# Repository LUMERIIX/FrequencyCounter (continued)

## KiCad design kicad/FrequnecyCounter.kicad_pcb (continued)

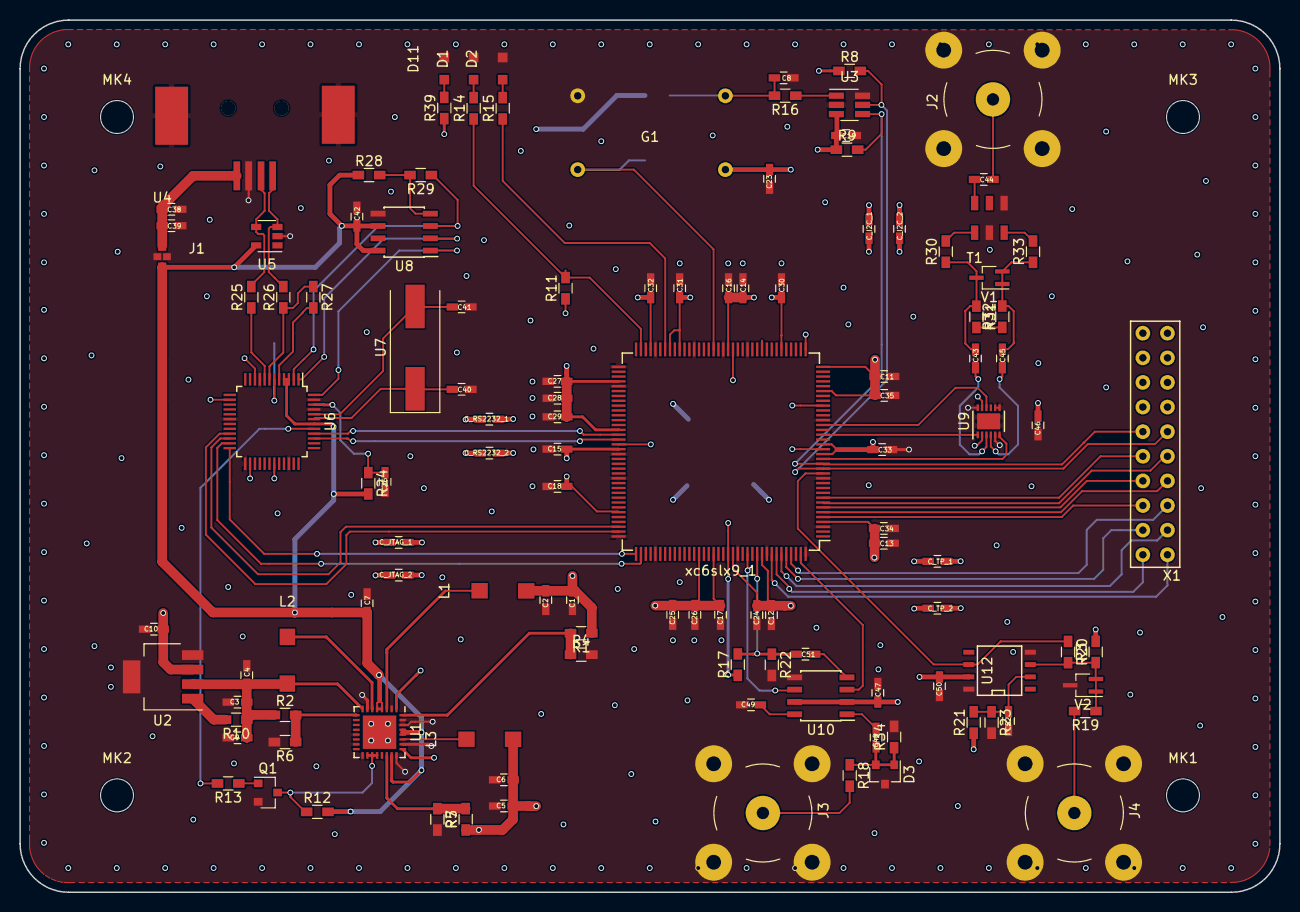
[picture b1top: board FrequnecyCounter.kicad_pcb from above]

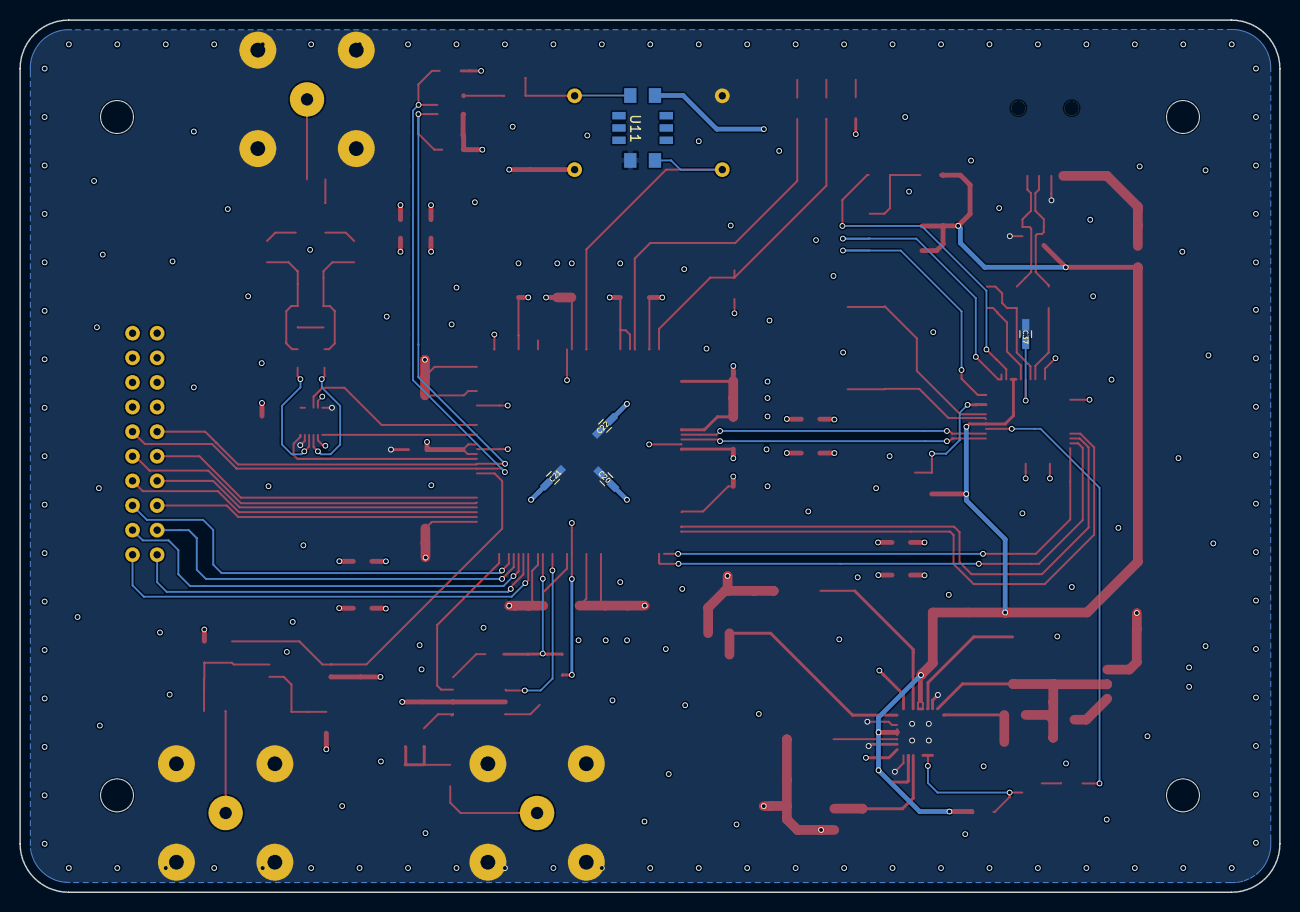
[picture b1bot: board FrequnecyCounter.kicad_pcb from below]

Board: 4 copper layers, 130.0 x 90.0 mm, 129 parts (5 on the bottom side), 80 nets.

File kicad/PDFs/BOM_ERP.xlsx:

| Description | Part | References | Value | Quantity Per PCB | ERP Nr. | Kontrolle Footprint | Quantity to Order
1 | Unpolarized capacitor | C | C18 C22 C25 C26 C28 C29 C31 C32 C34 C35 | 0.47u | 10 | 120048 | x | 0 | MG-07
2 | Unpolarized capacitor | C | C7 C19 C23 C39 C42 C43 C44 C45 C46 C47 | 100n | 10 | 101653 | x | 0 | MG-07
3 | Unpolarized capacitor | C | C51 | 100p | 1 | 118123 | x | 0 | MG-07
4 | Unpolarized capacitor | C | C1 C2 C3 C4 C5 C6 C9 C10 C38 | 10u | 9 | 101654 | x | 0 | MG-07
5 | Unpolarized capacitor | C | C48 C49 | 1n | 2 | 101606 | x | 0 | MG-07
6 | Unpolarized capacitor | C | C8 C_I2C_1 C_I2C_2 C_JTAG_1 C_JTAG_2 C_RS2232_1 C_RS2232_2 C_TP_1 C_TP_2 | 1u | 9 | 101655 | x | 0 | MG-07
7 | Unpolarized capacitor | C | C40 C41 | 27p | 2 | 115705 | x | 0 | MG-07
8 | Unpolarized capacitor | C | C36 C37 | 33n | 2 | 120245 | x | 0 | MG-07
9 | Unpolarized capacitor | C | C11 C12 C13 C14 C15 C16 C17 C20 C21 C24 C27 C30 C33 | 4.7u | 13 | 121207 | x | 0 | MG-07
10 | BAV99 High-speed switching diodes | BAV99 | D3 | BAV99 | 1 | 100569 | x | 0 | SMD_DIO 04
11 | LED generic | LED | D1 D2 D11 | LED | 3 | 121890 | x | 0 | MG-13
12 | AOCJY1-100MHz | AOCJY1-100MHz | G1 | AOCJY1-100MHz | 1 |  | x | 1
13 | coaxial connector (BNC, SMA, SMB, SMC, Cinch/RCA, ...) | CONN_COAXIAL | J2 J3 J4 | CONN_COAXIAL | 3 | 102877 | x | 0 | RH-095
14 | USB Type B connector | USB_B | J1 | USB_B | 1 | 103294 | x | 0 | MG-015
15 | Inductor with Ferrite Core | L_Core_Ferrite | L1 L2 L3 | 2.2u | 3 | 101900 | x | 0 | SMD-L / 08
16 | Resistor | R | R27 | 1.5k | 1 | 115747 | x | 0 | SMD-R / 06
17 | Resistor | R | R30 R33 | 100R | 2 | 101265 | x | 0 | SMD-R / 06
18 | Resistor | R | R2 R5 | 100k | 2 | 115771 | x | 0 | SMD-R / 07
19 | Resistor | R | R10 R28 | 10k | 2 | 101335 | x | 0 | SMD-R / 08
20 | Resistor | R | R1 R4 | 180k | 2 | 118873 | x | 0 | SMD-R / 09
21 | Resistor | R | R16 R12 | 1k | 2 | 101266 | x | 0 | SMD-R / 10
22 | Resistor | R | R29 | 2.2k | 1 | 115749 | x | 0 | SMD-R / 11
23 | Resistor | R | R6 | 20k | 1 | 124818 | x | 0 | SMD-R / 12
24 | Resistor | R | R7 | 22k | 1 | 101285 | x | 0 | SMD-R / 13
25 | Resistor | R | R25 R26 | 27R | 2 | 101255 | x | 0 | SMD-R / 14
26 | Resistor | R | R8 R9 R11 | 4.7k | 3 | 101332 | x | 0 | SMD-R / 15
27 | Resistor | R | R24 | 470R | 1 | 101329 | x | 0 | SMD-R / 16
28 | Resistor | R | R32 | 47R | 1 | 115728 | x | 0 | SMD-R / 17
29 | Resistor | R | R34 | 50R | 1 | 101318 | x | 0 | SMD-R / 18
30 | Resistor | R | R31 | 560R | 1 | 101284 | x | 0 | SMD-R / 19
31 | Resistor | R | R14 R15 R17 R22 R39 | 680R | 5 | 114094 | x | 0 | SMD-R / 20
33 | TC1-1T | WBC16-1T | T1 | WBC16-1T | 1 |  | x | 1
34 | 6MHz_Crystal | 6MHz_Crystal | U7 | 6MHz_Crystal | 1 | 101939 | x | 0 | SMD-QUA / 09
35 | AT93C46DN-SH | AT93C46DN-SH | U8 | AT93C46DN-SH | 1 | 121360 | x | 0 | MG-02
36 | Full Speed Double Channel USB UART/FIFO, LQFP-48 | FT2232D | U6 | FT2232D | 1 | 125249 | x | 1 | MG-02
37 | LP3870 | LP3871 | U2 | LP3871 | 1 |  | x | 1
38 | LTC6957-2 | LTC6957-3 | U9 | LTC6957-3 | 1 | 124015 | x | 0 | MG-02
39 | MC12092 | MC12093 | U10 | MC12093 | 1 | 120174 | x | 0 | MG-02
40 | MCP4724 | MCP4725 | U3 | MCP4725 | 1 | 119755 | x | 0 | MG-02
41 | NFM18PS | NFM18PS | U4 | NFM18PS | 1 | 118877 | x | 0 | MG-07
42 | TLV3500 | TLV3501 | U12 | TLV3501 | 1 |  | x | 1
43 | TPS650249 | TPS650250 | U1 | TPS650250 | 1 |  | x | 1
44 | WE-TVS-824010 | WE-TVS-824011 | U5 | WE-TVS-824011 | 1 | 119885 | x | 0 | MG-04
45 | tx175 | tx176 | U11 | tx176 | 1 |  | x | 1
46 | HSMS-281C-TR1G | HSMS-281C-TR1G | V1 V2 | HSMS-281C-TR1G | 2 | 124016 | x | 0 | MG-04
47 | Header_2x10Pf-R2.54 | Header_2x10Pf-R2.54 | X1 | Header_2x10Pf-R2.54 | 1 | 125569 | x | 1
48 | xc6slx9_143 | xc6slx9_144 | xc6slx9_1 | xc6slx9_144 | 1 |  | x | 1
49 | 45V Vce, 0.8A Ic, NPN, SOT-23 | BC846B | Q1 | BC846B | 1 | 100616 | x | 0 | SMD_TR / 05
50 | Resistor | R | R13 | 150k | 1 | 117827 | x | 0 | MG-06
28 | Resistor | R | R18 R19 | 330R | 2 | 101264 | x | 0 | MG-06
Quantity of PCBs | 1
 |  |  |  |  |  |  |  | 2
acrylglas | 130x90x2 |4x3.4 Loch 10mm abstand | entgratet |10mm radius |  | 2

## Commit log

2017-05-19 Add documentation files
2017-05-19 Edit Req&Specs
2017-06-15 Anpassungen und Änderungen von einigen präverierten Bauteilen
2017-07-14 Added planing BOM
2017-07-14 Add hardware layout
2017-07-17 Layout [in progress]
2017-08-22 Update Layout and Schematic [On Change]
2017-08-22 Add VHDL test files [ON CHANGE]
2017-08-30 - Delete multiple and useless files - Add DataController and Processor
2017-09-01 Update files [in progress]
2017-09-05 Bug fixes and add DataController features [in progress]
2017-09-14 Remove IEE.STD_LOGIC_UNSIGNED.ALL DataController adjusted output sequence
2017-09-18 Add working DataProcesssingUnit for the UART data
2017-09-19 Add working ChannelSelector
2017-09-19 Layout changes [in progress]
2017-10-09 Rework hardware schematic [in progress]
2017-10-10 Reworked schematic and layout [to review]
2017-10-11 Remove design errors and changes some footprints [to review]
2017-10-11 swaping power-plane layer with ground layer [to review]
2017-10-26 some small schematic and layout changes [completed]
2017-10-31 Add VHDL I2C master controller with wishbone interface
2017-10-31 clean up files
2017-11-02 Changed some Footprints to improve handsoldering
2017-11-02 Small layout and schematic changes
2017-11-06 Small schematic and layout changes
2017-11-06 Layout changes to guarantee the fit of the PCB housing
2017-11-07 Changed layout to guarantee to fit the housing
2017-11-07 Relocated overhanging USB connector
2017-11-09 Placed vias to stitch gnd planes together | Add blank pcb frame | Changed some panel positions
2017-11-14 Change location of i2c folder ==> Moved to VHDL
2017-11-14 layout commit after generating Gerberfiles
2017-11-14 Changed location of i2c folder to VHDL
2017-11-14 Add adjusted i2c_master_top.vhd for Zealot & Zpu4
2017-11-17 Changed I2C controller register addresses to solve communication issues
2017-11-21 Changed again I2C controller register adresses to reduce unnecessary accesses/traffic to the controller registers
2017-12-01 Changed control signal and fitted the selections to the communication protocol
2017-12-01 Changed output datatype to std_logic_vector to get a consistent datatpye in the hole project
2017-12-01 small changes | not necessary anymore | in the next commits it'll be replaced
2017-12-01 Add Escaping.vhd for the UART COM
2017-12-01 clean up | changed names | changes datatpyes and set firm datalength
2017-12-01 Implement Zealot ZPU and sidestuff |clean up | removed some obsolte components
2017-12-15 Changed project structure
2017-12-15 Add UartTop + new project structure
2017-12-15 Add I2CTop + new project structure
2017-12-15 Add FrequencyCounter_core + new project structure
2017-12-15 adjusted for FrequencyCounter and for simulating with ghdl
2017-12-15 Removed some unnecessary files for the new software structure
2018-01-09 Changed UART Config
2018-01-09 Changed entire project structure Project clean up
2018-01-09 Changed structure of FrequencyCounter component
2018-01-09 changed some addresses clean up
2018-01-09 small changes for ghdl simulation
2018-01-09 small changes for ghdl simulation & clean up
2018-01-09 small code refactoring & clean up
2018-01-09 small code refactoring & bug fixes & clean up
2018-01-12 Create Folder "Images" and "C"
2018-01-12 Add hardware pictures
2018-01-16 Set default values
2018-01-16 Clean up & reset bug fix
2018-01-16 Bug fix: change uart frequency to clk_speed value
2018-01-16 Clean up & add GPIOs for hardware controlling and testing
2018-01-16 Clean up & change ZPU addresses
2018-02-12 Changed some component values to increase the fit & Changed power-supply of the eeprom to use the PWR_EN of the FT2232D
2018-02-12 Add more hardware images for documentation
2018-02-12 changed divider for 10MHz ref.-clock
2018-02-12 changed testpoint layout for testing SigrokLcd
2018-02-12 Set Divider of channel A divider to /8 & Enabled FILTER for both channels of LTC6957
2018-02-16 Changed layout and translated german
2018-02-16 Remove obsolete Planning Files
2018-02-16 Changed Directory of Images and Add Documentation folder
2018-02-16 Add Image
2018-02-16 Add Documentation
2018-02-19 Add Images/Communication_Abstraction.png
2018-02-19 Add images and documentation files
2018-02-19 Add Images
2018-02-19 Add WishboneBridge VHDL file to manage all source files in the repo
2018-02-19 Add dualportRAM VHDL file to manage all source files in the repo
2018-02-19 Small changes with TPs
2018-02-19 Add dualportRAM VHDL file
2018-02-19 Remove link file
2018-02-19 Add folder bitstream & frequnecycountertop_v1.0.0.bit & pinout
2018-02-19 Add C-File
2018-02-19 Add folder FTDI with FT_Prog Template & ft2232 config-file for openocd
2018-08-08 clean up in layout & add exports (assembly drawings)
2018-08-23 new bitstream with non specific pin assignment & changed TP assignment
2018-08-24 Add alternative bitstream
2018-08-31 changed some install instructions
2018-08-31 Changed install instructions
2021-11-10 Update README.md
    https://forum.kicad.info/t/warning-avoid-all-links-to-kicad-pcb-org-use-kicad-org/31521
